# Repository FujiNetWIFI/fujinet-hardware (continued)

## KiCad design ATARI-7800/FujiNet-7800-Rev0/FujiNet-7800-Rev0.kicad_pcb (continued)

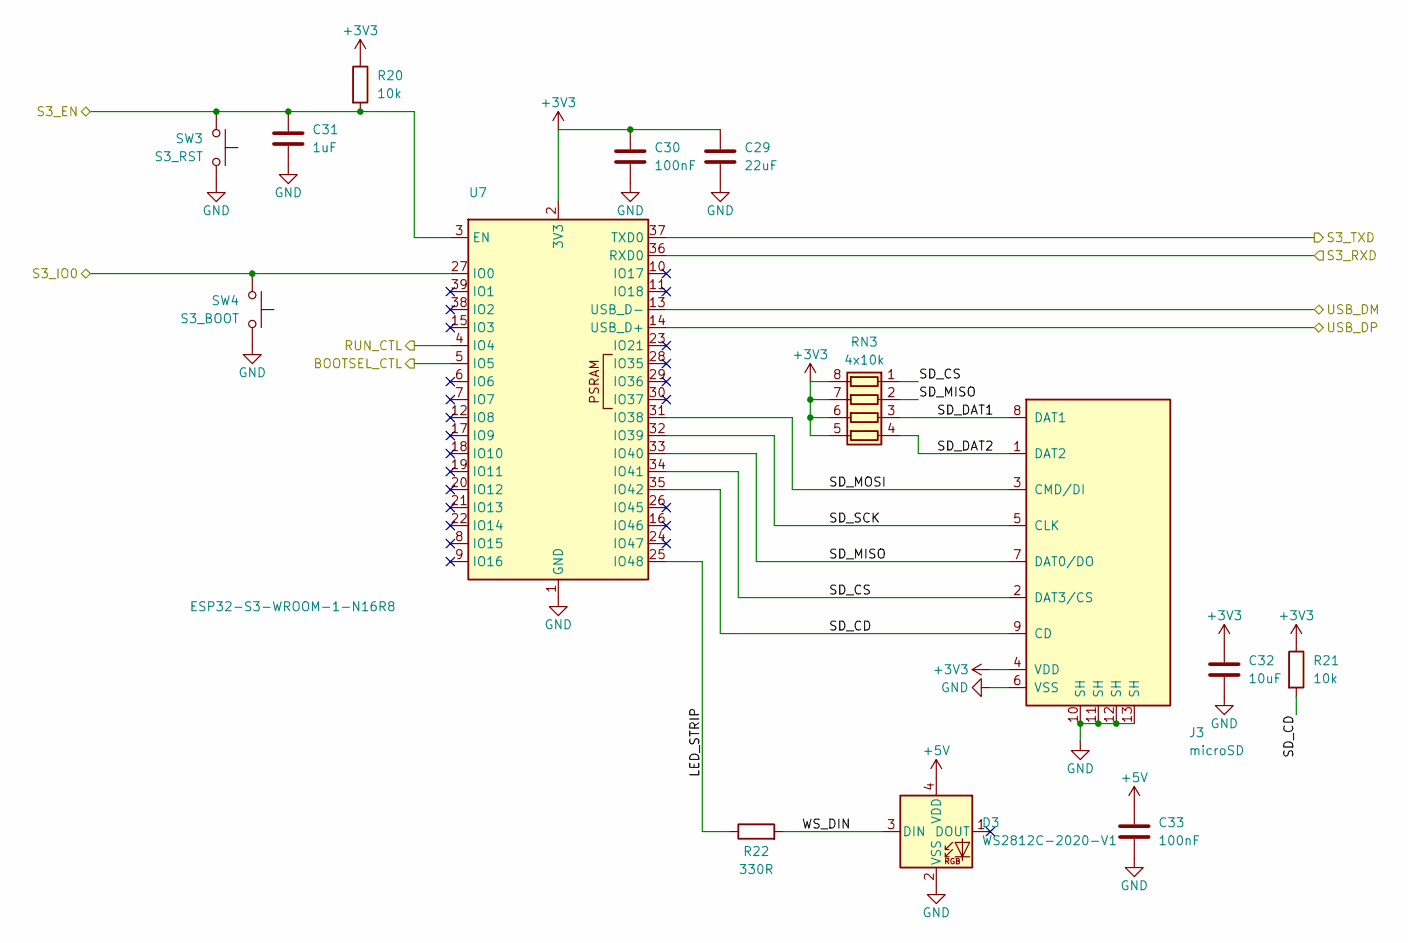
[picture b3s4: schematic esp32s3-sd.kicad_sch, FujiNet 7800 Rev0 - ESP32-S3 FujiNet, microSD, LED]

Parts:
C29: 22uF; C_0805_2012Metric; MPN CL21A226MAQNNNE; LCSC C45783
C30, C33: 100nF; C_0603_1608Metric; MPN CC0603KRX7R9BB104; LCSC C14663
C31: 1uF; C_0603_1608Metric; MPN CL10A105KB8NNNC; LCSC C15849
C32: 10uF; C_0603_1608Metric; MPN CL10A106KP8NNNC; LCSC C19702
D3: WS2812C-2020-V1; LED_WS2812B-2020_PLCC4_2.0x2.0mm; MPN WS2812C-2020-V1; LCSC C2976072
J3: microSD; TF-SMD_TF-015; MPN TF-015; LCSC C113206
R20, R21: 10k; R_0603_1608Metric; MPN 0603WAF1002T5E; LCSC C25804
R22: 330R; R_0603_1608Metric; MPN 0603WAF3300T5E; LCSC C23138
RN3: 4x10k; R_Array_Convex_4x0603; MPN 4D03WGJ0103T5E; LCSC C29718
SW3: S3_RST; SW_SPST_TS-1187A; MPN TS-1187A-B-A-B; LCSC C318884
SW4: S3_BOOT; SW_SPST_TS-1187A; MPN TS-1187A-B-A-B; LCSC C318884
U7: ESP32-S3-WROOM-1-N16R8; ESP32-S3-WROOM-1; MPN ESP32-S3-WROOM-1-N16R8; LCSC C2913202

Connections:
+3V3: C29.1, C30.1, C32.1, J3.4 (VDD), R20.1, R21.1, RN3.5 (R4.2), RN3.6 (R3.2), RN3.7 (R2.2), RN3.8 (R1.2), U7.2 (3V3); also elsewhere on the board
+5V: C33.1, D3.4 (VDD); also elsewhere on the board
/BOOTSEL_CTL: U7.5 (IO5); also elsewhere on the board
/RUN_CTL: U7.4 (IO4); also elsewhere on the board
/S3_EN: C31.1, R20.2, SW3.1, U7.3 (EN); also elsewhere on the board
/S3_IO0: SW4.1, U7.27 (IO0); also elsewhere on the board
/S3_RXD: U7.36 (RXD0); also elsewhere on the board
/S3_TXD: U7.37 (TXD0); also elsewhere on the board
/USB_DM: U7.13 (USB_D-); also elsewhere on the board
/USB_DP: U7.14 (USB_D+); also elsewhere on the board
/esp32s3-sd/LED_STRIP: R22.1, U7.25 (IO48)
/esp32s3-sd/SD_CD: J3.9 (CD), R21.2, U7.35 (IO42)
/esp32s3-sd/SD_CS: J3.2 (DAT3/CS), RN3.1 (R1.1), U7.34 (IO41)
/esp32s3-sd/SD_DAT1: J3.8 (DAT1), RN3.3 (R3.1)
/esp32s3-sd/SD_DAT2: J3.1 (DAT2), RN3.4 (R4.1)
/esp32s3-sd/SD_MISO: J3.7 (DAT0/DO), RN3.2 (R2.1), U7.33 (IO40)
/esp32s3-sd/SD_MOSI: J3.3 (CMD/DI), U7.31 (IO38)
/esp32s3-sd/SD_SCK: J3.5 (CLK), U7.32 (IO39)
/esp32s3-sd/WS_DIN: D3.3 (DIN), R22.2
GND: C29.2, C30.2, C31.2, C32.2, C33.2, D3.2 (VSS), J3.6 (VSS), J3.10 (SH), J3.11 (SH), J3.12 (SH), J3.13 (SH), SW3.2, SW4.2, U7.1 (GND), U7.40 (GND), U7.41 (GND); also elsewhere on the board

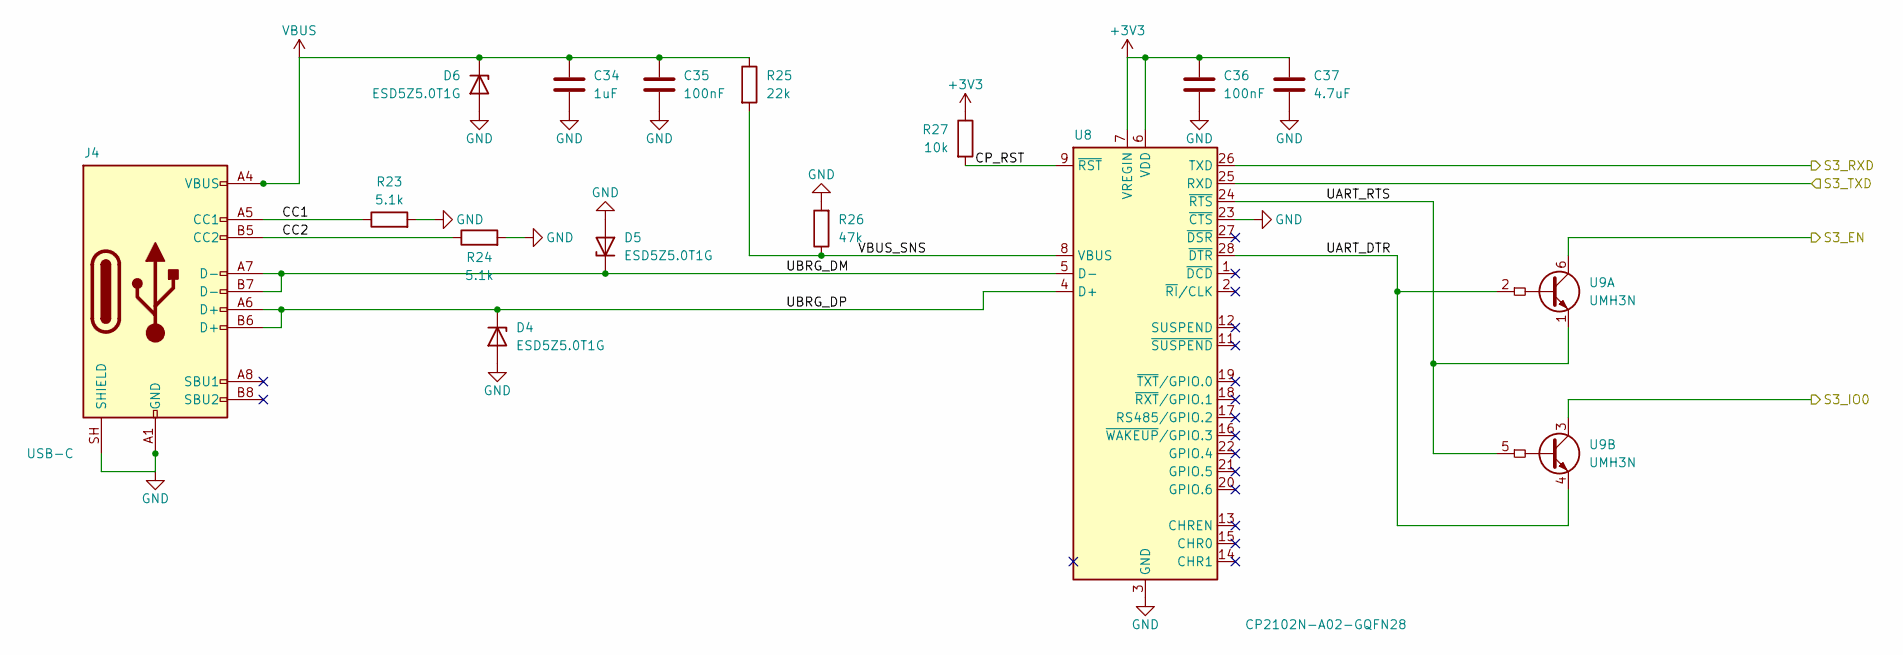
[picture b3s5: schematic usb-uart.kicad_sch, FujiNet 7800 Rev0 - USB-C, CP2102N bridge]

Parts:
C34: 1uF; C_0603_1608Metric; MPN CL10A105KB8NNNC; LCSC C15849
C35, C36: 100nF; C_0603_1608Metric; MPN CC0603KRX7R9BB104; LCSC C14663
C37: 4.7uF; C_0603_1608Metric; MPN CL10A475KO8NNNC; LCSC C19666
D4, D5, D6: ESD5Z5.0T1G; D_SOD-523; MPN ESD5Z5.0T1G; LCSC C82044
J4: USB-C; USB_C_Receptacle_HRO_TYPE-C-31-M-12; MPN TYPE-C-31-M-12; LCSC C165948
R23, R24: 5.1k; R_0603_1608Metric; MPN 0603WAF5101T5E; LCSC C23186
R25: 22k; R_0603_1608Metric; MPN 0603WAF2202T5E; LCSC C31850
R26: 47k; R_0603_1608Metric; MPN 0603WAF4702T5E; LCSC C25819
R27: 10k; R_0603_1608Metric; MPN 0603WAF1002T5E; LCSC C25804
U8: CP2102N-A02-GQFN28; QFN-28-1EP_5x5mm_P0.5mm_EP3.35x3.35mm; MPN CP2102N-A02-GQFN28R; LCSC C964632
U9: UMH3N; SOT-363_SC-70-6; MPN UMH3N; LCSC C62892

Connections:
+3V3: C36.1, C37.1, R27.1, U8.6 (VDD), U8.7 (VREGIN); also elsewhere on the board
/S3_EN: U9.6 (C1); also elsewhere on the board
/S3_IO0: U9.3 (C2); also elsewhere on the board
/S3_RXD: U8.26 (TXD); also elsewhere on the board
/S3_TXD: U8.25 (RXD); also elsewhere on the board
/usb-uart/CC1: J4.A5 (CC1), R23.1
/usb-uart/CC2: J4.B5 (CC2), R24.1
/usb-uart/CP_RST: R27.2, U8.9 (~RST)
/usb-uart/UART_DTR: U8.28 (~DTR), U9.2 (B1), U9.4 (E2)
/usb-uart/UART_RTS: U8.24 (~RTS), U9.1 (E1), U9.5 (B2)
/usb-uart/UBRG_DM: D5.1 (K), J4.A7 (D-), J4.B7 (D-), U8.5 (D-)
/usb-uart/UBRG_DP: D4.1 (K), J4.A6 (D+), J4.B6 (D+), U8.4 (D+)
/usb-uart/VBUS_SNS: R25.2, R26.1, U8.8 (VBUS)
GND: C34.2, C35.2, C36.2, C37.2, D4.2 (A), D5.2 (A), D6.2 (A), J4.A1 (GND), J4.A12 (GND), J4.B1 (GND), J4.B12 (GND), J4.SH (SHIELD), R23.2, R24.2, R26.2, U8.3 (GND), U8.23 (~CTS), U8.29 (GND); also elsewhere on the board
VBUS: C34.1, C35.1, D6.1 (K), J4.A4 (VBUS), J4.A9 (VBUS), J4.B4 (VBUS), J4.B9 (VBUS), R25.1; also elsewhere on the board

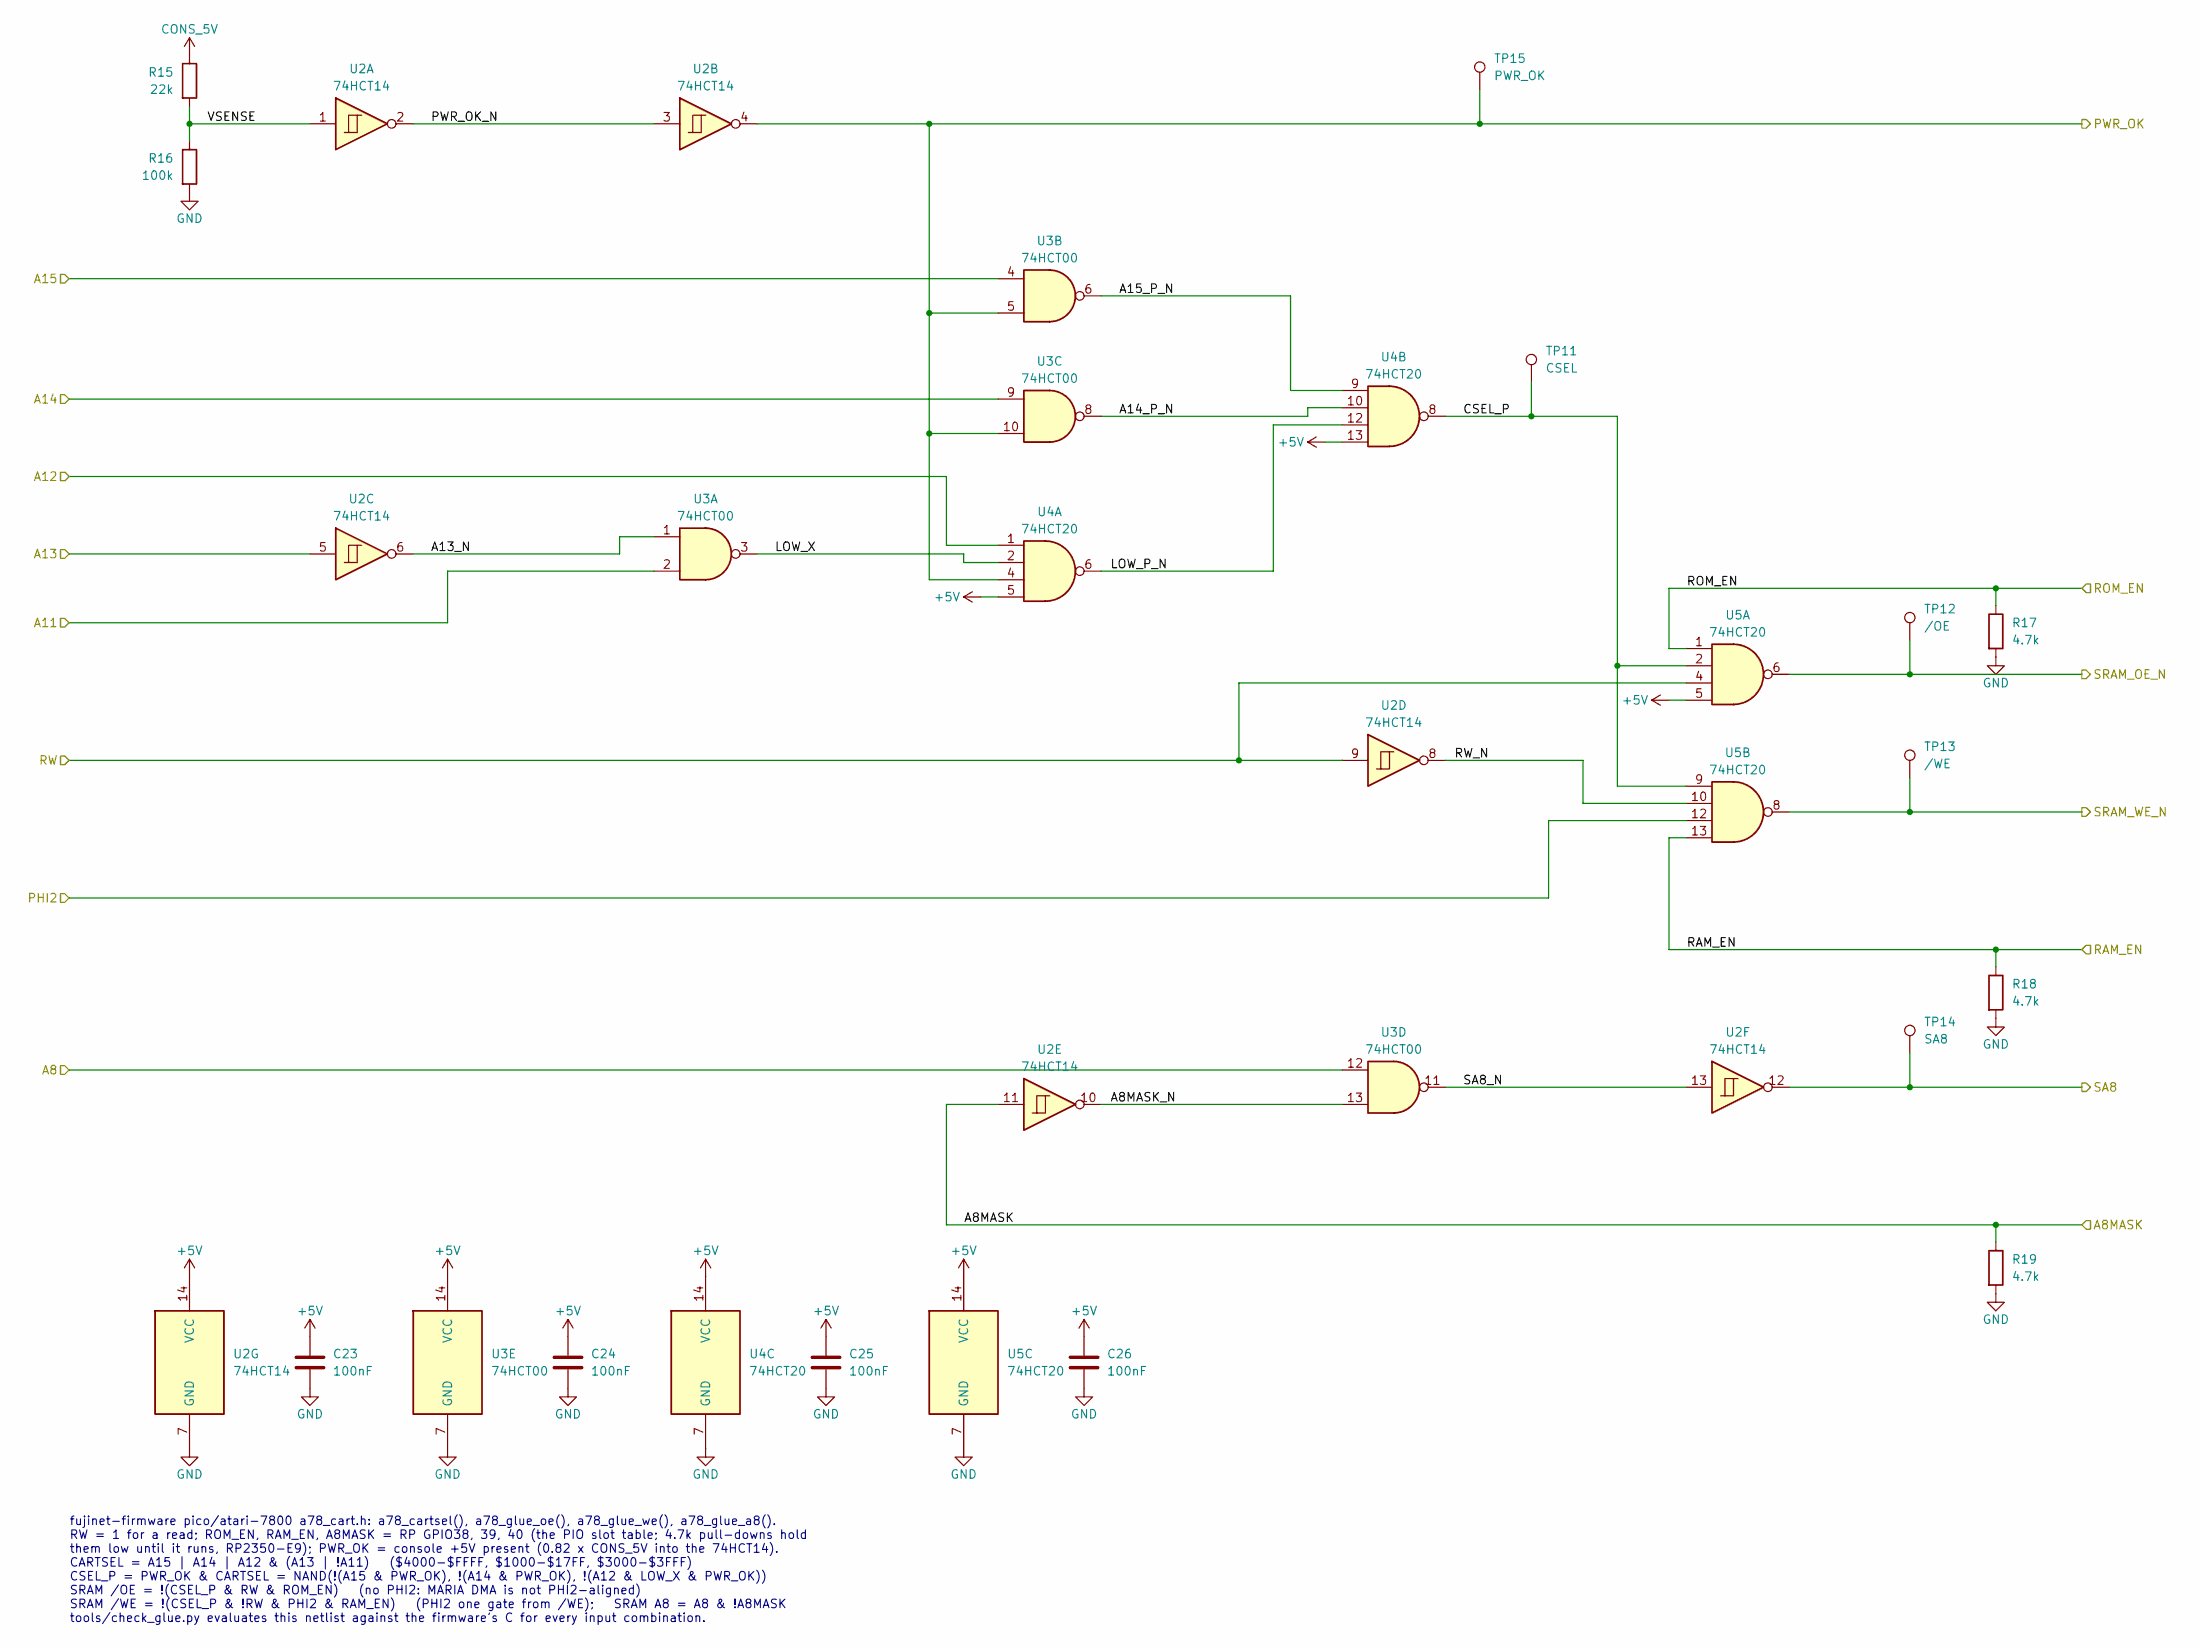
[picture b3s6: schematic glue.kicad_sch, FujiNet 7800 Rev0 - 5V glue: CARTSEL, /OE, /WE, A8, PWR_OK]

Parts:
C23, C24, C25, C26: 100nF; C_0603_1608Metric; MPN CC0603KRX7R9BB104; LCSC C14663
R15: 22k; R_0603_1608Metric; MPN 0603WAF2202T5E; LCSC C31850
R16: 100k; R_0603_1608Metric; MPN 0603WAF1003T5E; LCSC C25803
R17, R18, R19: 4.7k; R_0603_1608Metric; MPN 0603WAF4701T5E; LCSC C23162
TP11: CSEL; TestPoint_Pad_D1.5mm
TP12: /OE; TestPoint_Pad_D1.5mm
TP13: /WE; TestPoint_Pad_D1.5mm
TP14: SA8; TestPoint_Pad_D1.5mm
TP15: PWR_OK; TestPoint_Pad_D1.5mm
U2: 74HCT14; SOIC-14_3.9x8.7mm_P1.27mm; MPN SN74HCT14DR; LCSC C6769
U3: 74HCT00; SOIC-14_3.9x8.7mm_P1.27mm; MPN SN74HCT00DR; LCSC C6764
U4, U5: 74HCT20; SOIC-14_3.9x8.7mm_P1.27mm; MPN CD74HCT20M96; LCSC C2878717

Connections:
+5V: C23.1, C24.1, C25.1, C26.1, U2.14 (VCC), U3.14 (VCC), U4.5, U4.13, U4.14 (VCC), U5.5, U5.14 (VCC); also elsewhere on the board
/A8: U3.12; also elsewhere on the board
/A8MASK: R19.1, U2.11; also elsewhere on the board
/A11: U3.2; also elsewhere on the board
/A12: U4.1; also elsewhere on the board
/A13: U2.5; also elsewhere on the board
/A14: U3.9; also elsewhere on the board
/A15: U3.4; also elsewhere on the board
/PHI2: U5.12; also elsewhere on the board
/PWR_OK: TP15.1, U2.4, U3.5, U3.10, U4.4; also elsewhere on the board
/RAM_EN: R18.1, U5.13; also elsewhere on the board
/ROM_EN: R17.1, U5.1; also elsewhere on the board
/RW: U2.9, U5.4; also elsewhere on the board
/SA8: TP14.1, U2.12; also elsewhere on the board
/SRAM_OE_N: TP12.1, U5.6; also elsewhere on the board
/SRAM_WE_N: TP13.1, U5.8; also elsewhere on the board
/glue/A8MASK_N: U2.10, U3.13
/glue/A13_N: U2.6, U3.1
/glue/A14_P_N: U3.8, U4.10
/glue/A15_P_N: U3.6, U4.9
/glue/CSEL_P: TP11.1, U4.8, U5.2, U5.9
/glue/LOW_P_N: U4.6, U4.12
/glue/LOW_X: U3.3, U4.2
/glue/PWR_OK_N: U2.2, U2.3
/glue/RW_N: U2.8, U5.10
/glue/SA8_N: U2.13, U3.11
/glue/VSENSE: R15.2, R16.1, U2.1
CONS_5V: R15.1; also elsewhere on the board
GND: C23.2, C24.2, C25.2, C26.2, R16.2, R17.2, R18.2, R19.2, U2.7 (GND), U3.7 (GND), U4.7 (GND), U5.7 (GND); also elsewhere on the board

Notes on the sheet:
fujinet-firmware pico/atari-7800 a78_cart.h: a78_cartsel(), a78_glue_oe(), a78_glue_we(), a78_glue_a8(). RW = 1 for a read; ROM_EN, RAM_EN, A8MASK = RP GPIO38, 39, 40 (the PIO slot table; 4.7k pull-downs hold them low until it runs, RP2350-E9); PWR_OK = console +5V present (0.82 x CONS_5V into the 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

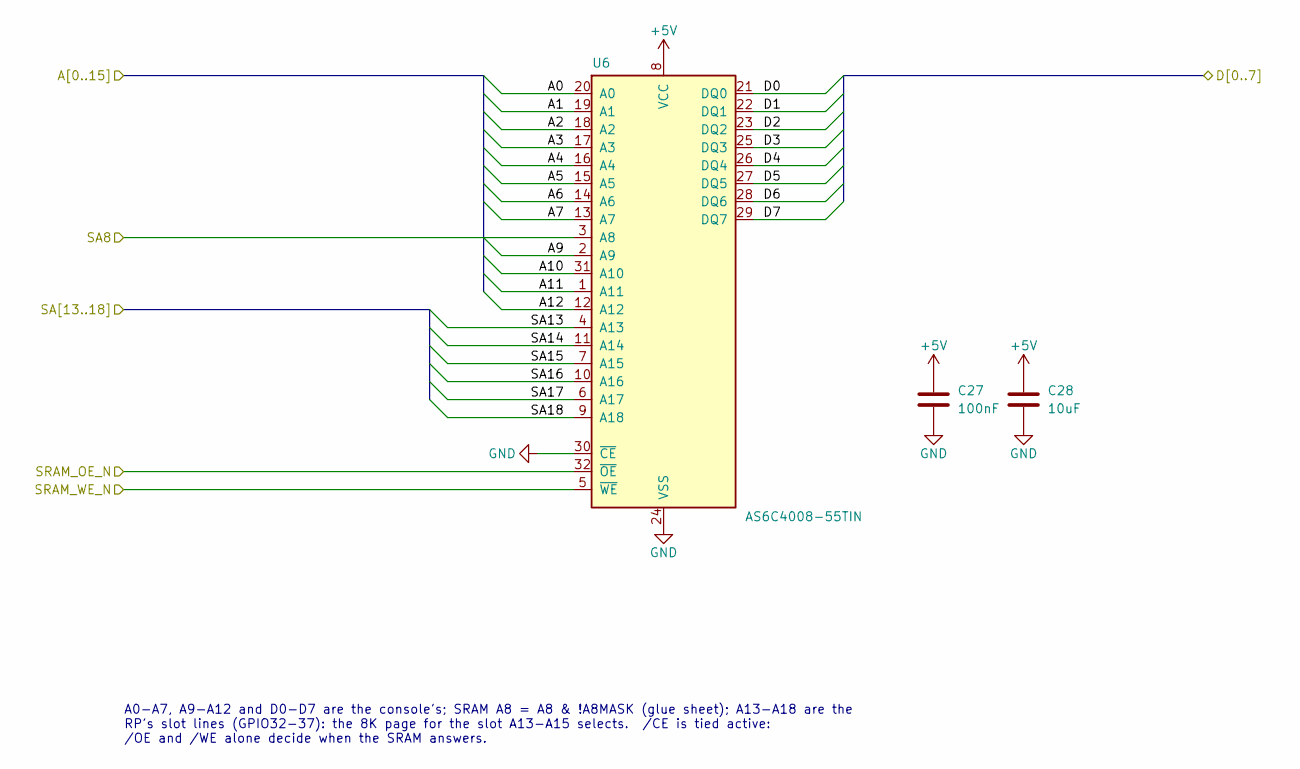
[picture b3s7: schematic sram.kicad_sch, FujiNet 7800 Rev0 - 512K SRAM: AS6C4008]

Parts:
C27: 100nF; C_0603_1608Metric; MPN CC0603KRX7R9BB104; LCSC C14663
C28: 10uF; C_0603_1608Metric; MPN CL10A106KP8NNNC; LCSC C19702
U6: AS6C4008-55TIN; TSOP-I-32_18.4x8mm_P0.5mm; MPN AS6C4008-55TIN; LCSC C5569980

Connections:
+5V: C27.1, C28.1, U6.8 (VCC); also elsewhere on the board
/A0: U6.20 (A0); also elsewhere on the board
/A1: U6.19 (A1); also elsewhere on the board
/A2: U6.18 (A2); also elsewhere on the board
/A3: U6.17 (A3); also elsewhere on the board
/A4: U6.16 (A4); also elsewhere on the board
/A5: U6.15 (A5); also elsewhere on the board
/A6: U6.14 (A6); also elsewhere on the board
/A7: U6.13 (A7); also elsewhere on the board
/A9: U6.2 (A9); also elsewhere on the board
/A10: U6.31 (A10); also elsewhere on the board
/A11: U6.1 (A11); also elsewhere on the board
/A12: U6.12 (A12); also elsewhere on the board
/D0: U6.21 (DQ0); also elsewhere on the board
/D1: U6.22 (DQ1); also elsewhere on the board
/D2: U6.23 (DQ2); also elsewhere on the board
/D3: U6.25 (DQ3); also elsewhere on the board
/D4: U6.26 (DQ4); also elsewhere on the board
/D5: U6.27 (DQ5); also elsewhere on the board
/D6: U6.28 (DQ6); also elsewhere on the board
/D7: U6.29 (DQ7); also elsewhere on the board
/SA8: U6.3 (A8); also elsewhere on the board
/SA13: U6.4 (A13); also elsewhere on the board
/SA14: U6.11 (A14); also elsewhere on the board
/SA15: U6.7 (A15); also elsewhere on the board
/SA16: U6.10 (A16); also elsewhere on the board
/SA17: U6.6 (A17); also elsewhere on the board
/SA18: U6.9 (A18); also elsewhere on the board
/SRAM_OE_N: U6.32 (~OE); also elsewhere on the board
/SRAM_WE_N: U6.5 (~WE); also elsewhere on the board
GND: C27.2, C28.2, U6.24 (VSS), U6.30 (~CE); also elsewhere on the board

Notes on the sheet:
A0-A7, A9-A12 and D0-D7 are the console's; SRAM A8 = A8 & !A8MASK (glue sheet); A13-A18 are the RP's slot lines (GPIO32-37): the 8K page for the slot A13-A15 selects. /CE is tied active: /OE and /WE alone decide when the SRAM answers.

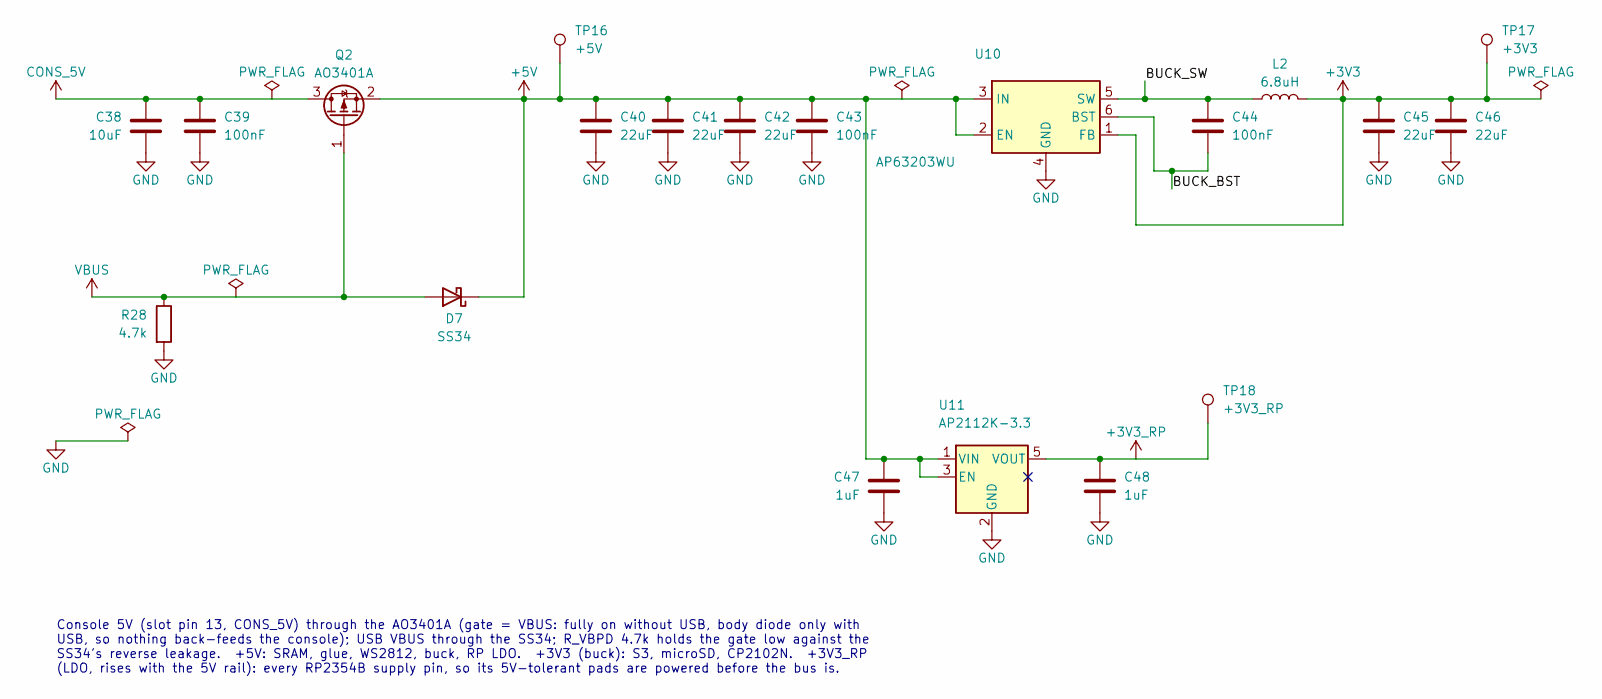
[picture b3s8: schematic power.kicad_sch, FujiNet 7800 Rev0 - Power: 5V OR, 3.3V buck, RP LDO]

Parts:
C38: 10uF; C_0603_1608Metric; MPN CL10A106KP8NNNC; LCSC C19702
C39, C43, C44: 100nF; C_0603_1608Metric; MPN CC0603KRX7R9BB104; LCSC C14663
C40, C41, C42, C45, C46: 22uF; C_0805_2012Metric; MPN CL21A226MAQNNNE; LCSC C45783
C47, C48: 1uF; C_0603_1608Metric; MPN CL10A105KB8NNNC; LCSC C15849
D7: SS34; D_SMA; MPN SS34; LCSC C8678
L2: 6.8uH; L_Sunlord_SWPA4030S; MPN SWPA4030S6R8MT; LCSC C62684
Q2: AO3401A; SOT-23; MPN AO3401A; LCSC C15127
R28: 4.7k; R_0603_1608Metric; MPN 0603WAF4701T5E; LCSC C23162
TP16: +5V; TestPoint_Pad_D1.5mm
TP17: +3V3; TestPoint_Pad_D1.5mm
TP18: +3V3_RP; TestPoint_Pad_D1.5mm
U10: AP63203WU; TSOT-23-6; MPN AP63203WU-7; LCSC C780769
U11: AP2112K-3.3; SOT-23-5; MPN AP2112K-3.3TRG1; LCSC C51118

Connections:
+3V3: C45.1, C46.1, L2.2, TP17.1, U10.1 (FB); also elsewhere on the board
+3V3_RP: C48.1, TP18.1, U11.5 (VOUT); also elsewhere on the board
+5V: C40.1, C41.1, C42.1, C43.1, C47.1, D7.1 (K), Q2.2 (S), TP16.1, U10.2 (EN), U10.3 (IN), U11.1 (VIN), U11.3 (EN); also elsewhere on the board
/power/BUCK_BST: C44.2, U10.6 (BST)
/power/BUCK_SW: C44.1, L2.1, U10.5 (SW)
CONS_5V: C38.1, C39.1, Q2.3 (D); also elsewhere on the board
GND: C38.2, C39.2, C40.2, C41.2, C42.2, C43.2, C45.2, C46.2, C47.2, C48.2, R28.2, U10.4 (GND), U11.2 (GND); also elsewhere on the board
VBUS: D7.2 (A), Q2.1 (G), R28.1; also elsewhere on the board

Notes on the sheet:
Console 5V (slot pin 13, CONS_5V) through the AO3401A (gate = VBUS: fully on without USB, body diode only with USB, so nothing back-feeds the console); USB VBUS through the SS34; R_VBPD 4.7k holds the gate low against the SS34's reverse leakage. +5V: SRAM, glue, WS2812, buck, RP LDO. +3V3 (buck): S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

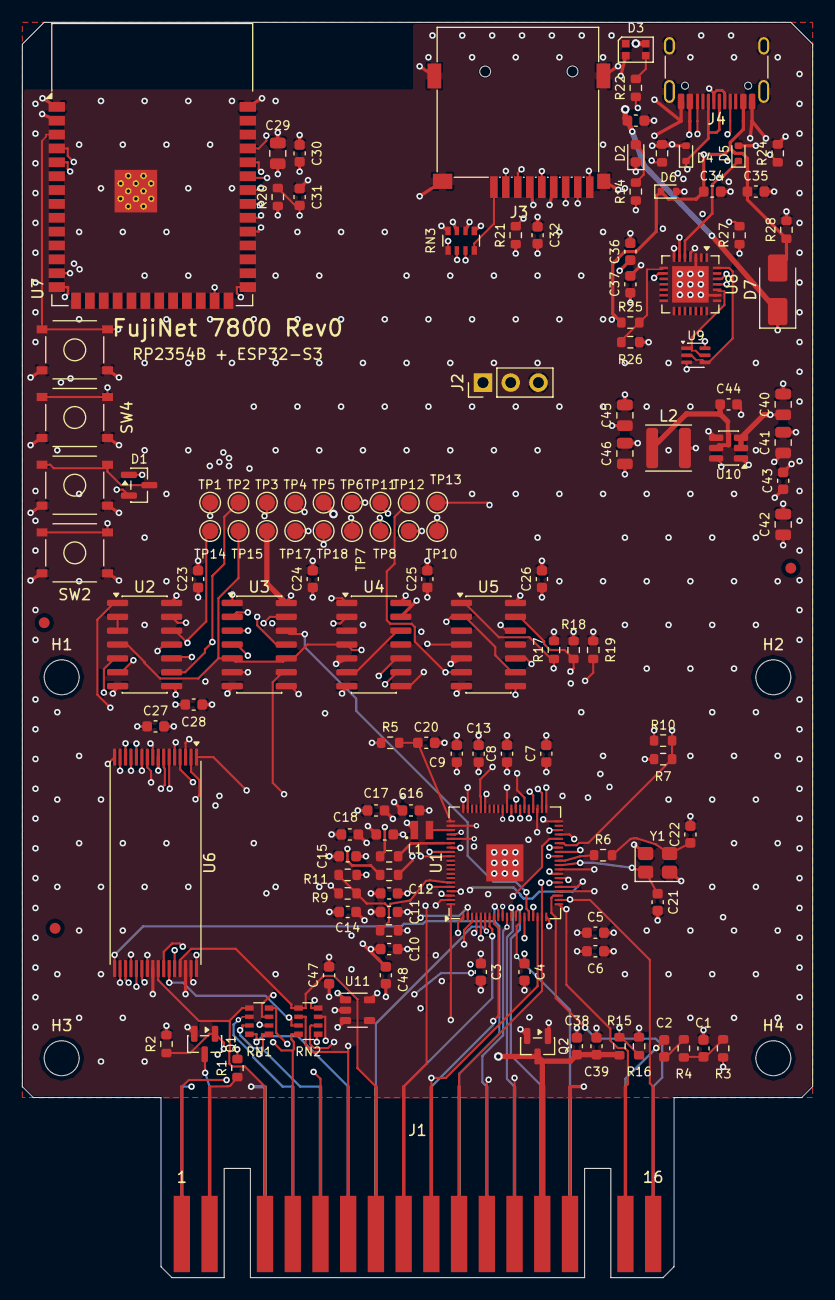
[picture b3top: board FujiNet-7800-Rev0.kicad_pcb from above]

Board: 6 copper layers, 72.4 x 115.0 mm, 135 parts (0 on the bottom side), 117 nets.

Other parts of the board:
FID1, FID2, FID3: Fiducial_1mm_Mask2mm
H1, H2, H3, H4: MountingHole_3.2mm_NPTH

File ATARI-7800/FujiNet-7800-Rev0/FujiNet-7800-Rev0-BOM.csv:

"Refs","Value","Footprint","MPN","Manufacturer","LCSC","Description","DNP"
"C1","10nF","C_0603_1608Metric","0603B103K500NT","Fenghua (FH)","C57112","audio PWM low-pass, fc 10.6 kHz",""
"C2,C31,C34,C47,C48","1uF","C_0603_1608Metric","CL10A105KB8NNNC","Samsung Electro-Mechanics","C15849","EAUDIO DC block",""
"C3,C4,C5,C6,C7,C8,C9,C10,C11,C12,C13,C16,C17,C18,C23,C24,C25,C26,C27,C30,C33,C35,C36,C39,C43,C44","100nF","C_0603_1608Metric","CC0603KRX7R9BB104","YAGEO","C14663","IOVDD decoupling",""
"C14,C28,C32,C38","10uF","C_0603_1608Metric","CL10A106KP8NNNC","Samsung Electro-Mechanics","C19702","RP IO rail bulk (LDO output)",""
"C15,C19,C20,C37","4.7uF","C_0603_1608Metric","CL10A475KO8NNNC","Samsung Electro-Mechanics","C19666","VREG_VIN bulk (LDO rail)",""
"C21,C22","15pF","C_0603_1608Metric","CL10C150JB8NNNC","Samsung Electro-Mechanics","C1644","crystal load",""
"C29,C40,C41,C42,C45,C46","22uF","C_0805_2012Metric","CL21A226MAQNNNE","Samsung Electro-Mechanics","C45783","S3 bulk (WiFi TX bursts)",""
"D1","BAT54C","SOT-23","BAT54C,215","Nexperia","C37704","RESET steering, common cathode",""
"D2","red","LED_0603_1608Metric","KT-0603R","Hubei KENTO Elec","C2286","activity LED (GPIO30)",""
"D3","WS2812C-2020-V1","LED_WS2812B-2020_PLCC4_2.0x2.0mm","WS2812C-2020-V1","Worldsemi","C2976072","status LED on +5V (datasheet VDD 3.7-5.3 V; VIH 2.7 V takes the S3 3.3 V data directly)",""
"D4,D5,D6","ESD5Z5.0T1G","D_SOD-523","ESD5Z5.0T1G","onsemi","C82044","ESD",""
"D7","SS34","D_SMA","SS34","MDD (Microdiode Semiconductor)","C8678","USB VBUS OR-ing (no back-feed into the console)",""
"J2","DBG UART","PinHeader_1x03_P2.54mm_Vertical","PZ254V-11-03P","XFCN","C2937625","RP debug UART, 3.3 V: 1 TX (GPIO44), 2 RX (GPIO45), 3 GND; fit for bring-up","DNP"
"J3","microSD","TF-SMD_TF-015","TF-015","SOFNG","C113206","microSD push-push, SPI mode",""
"J4","USB-C","USB_C_Receptacle_HRO_TYPE-C-31-M-12","TYPE-C-31-M-12","Korean Hroparts Elec","C165948","power + S3 programming",""
"L1","3.3uH","RPI_L_AOTA-B201610S3R3","AOTA-B201610S3R3-101-T","Abracon","C42411119","RP2350 core SMPS inductor",""
"L2","6.8uH","L_Sunlord_SWPA4030S","SWPA4030S6R8MT","Sunlord","C62684","buck inductor",""
"Q1","2N7002","SOT-23","2N7002","Jiangsu Changjing (JSCJ)","C8545","console /IRQ pull-down (G = GPIO28); never asserted",""
"Q2","AO3401A","SOT-23","AO3401A","Alpha & Omega Semiconductor","C15127","console 5V switch: G = VBUS, S = +5V, D = CONS_5V; body diode CONS_5V -> +5V",""
"R1,R2,R4,R7,R8,R20,R21,R27","10k","R_0603_1608Metric","0603WAF1002T5E","UNI-ROYAL","C25804","/HALT isolation: the console sees only the finger stub",""
"R3","1.5k","R_0603_1608Metric","0603WAF1501T5E","UNI-ROYAL","C22843","audio PWM low-pass, fc 10.6 kHz",""
"R5","33R","R_0603_1608Metric","0603WAF330JT5E","UNI-ROYAL","C23140","VREG_AVDD filter",""
"R6,R9,R10,R11,R14","1k","R_0603_1608Metric","0603WAF1001T5E","UNI-ROYAL","C21190","crystal drive limit",""
"R12,R13","27R","R_0603_1608Metric","0603WAF270JT5E","UNI-ROYAL","C25190","USB series",""
"R15,R25","22k","R_0603_1608Metric","0603WAF2202T5E","UNI-ROYAL","C31850","console 5V sense divider",""
"R16","100k","R_0603_1608Metric","0603WAF1003T5E","UNI-ROYAL","C25803","console 5V sense -> 0.82 x CONS_5V",""
"R17,R18,R19,R28","4.7k","R_0603_1608Metric","0603WAF4701T5E","UNI-ROYAL","C23162","ROM_EN low until the PIO table runs (RP2350-E9: <= 8.2k)",""
"R22","330R","R_0603_1608Metric","0603WAF3300T5E","UNI-ROYAL","C23138","WS2812 data series",""
"R23,R24","5.1k","R_0603_1608Metric","0603WAF5101T5E","UNI-ROYAL","C23186","UFP Rd",""
"R26","47k","R_0603_1608Metric","0603WAF4702T5E","UNI-ROYAL","C25819","VBUS sense divider",""
"RN1,RN2","4x100R","R_Array_Convex_4x0603","4D03WGJ0101T5E","UNI-ROYAL","C25506","D0-D3 100R series (GPIO0-3)",""
"RN3","4x10k","R_Array_Convex_4x0603","4D03WGJ0103T5E","UNI-ROYAL","C29718","SD pull-ups",""
"SW1","RESET","SW_SPST_TS-1187A","TS-1187A-B-A-B","XKB Connection","C318884","cart RESET: RP RUN + S3 EN via BAT54C",""
"SW2","BOOTSEL","SW_SPST_TS-1187A","TS-1187A-B-A-B","XKB Connection","C318884","RP2354 BOOTSEL (hold while pressing RESET)",""
"SW3","S3_RST","SW_SPST_TS-1187A","TS-1187A-B-A-B","XKB Connection","C318884","ESP32-S3 EN",""
"SW4","S3_BOOT","SW_SPST_TS-1187A","TS-1187A-B-A-B","XKB Connection","C318884","ESP32-S3 BOOT (IO0)",""
"U1","RP2354B","QFN-80-1EP_10x10mm_P0.4mm_EP3.4x3.4mm","RP2354B","Raspberry Pi","C39843328","RP2350B + 2MB flash in package; cart bus server + slot table",""
"U2","74HCT14","SOIC-14_3.9x8.7mm_P1.27mm","SN74HCT14DR","Texas Instruments","C6769","PWR_OK from the console 5V sense; A13, R/W, A8MASK, SRAM A8 inversions",""
"U3","74HCT00","SOIC-14_3.9x8.7mm_P1.27mm","SN74HCT00DR","Texas Instruments","C6764","LOW_X = A13 | !A11; A15, A14 & PWR_OK; SRAM A8 mask",""
"U4,U5","74HCT20","SOIC-14_3.9x8.7mm_P1.27mm","CD74HCT20M96","Texas Instruments","C2878717","CSEL_P = PWR_OK & CARTSEL",""
"U6","AS6C4008-55TIN","TSOP-I-32_18.4x8mm_P0.5mm","AS6C4008-55TIN","Alliance Memory","C5569980","512Kx8 SRAM, 5 V: 64 x 8K pages, slot page from the PIO table",""
"U7","ESP32-S3-WROOM-1-N16R8","ESP32-S3-WROOM-1","ESP32-S3-WROOM-1-N16R8","Espressif","C2913202","FujiNet core (fujiversal-atari7800)",""
"U8","CP2102N-A02-GQFN28","QFN-28-1EP_5x5mm_P0.5mm_EP3.35x3.35mm","CP2102N-A02-GQFN28R","Silicon Labs","C964632","USB-UART for S3 flashing/console (self-powered)",""
"U9","UMH3N","SOT-363_SC-70-6","UMH3N","Jiangsu Changjing (JSCJ)","C62892","esptool auto-program (DevKitC-1 style)",""
"U10","AP63203WU","TSOT-23-6","AP63203WU-7","Diodes Incorporated","C780769","3.3V 2A buck",""
"U11","AP2112K-3.3","SOT-23-5","AP2112K-3.3TRG1","Diodes Incorporated","C51118","RP2354B 3.3V LDO (IOVDD, VREG_VIN, VREG_AVDD), 600mA, fast start",""
"Y1","12MHz","Crystal_SMD_3225-4Pin_3.2x2.5mm","ABM8-272-T3","Abracon","C20625731","RP2350 12 MHz crystal",""
